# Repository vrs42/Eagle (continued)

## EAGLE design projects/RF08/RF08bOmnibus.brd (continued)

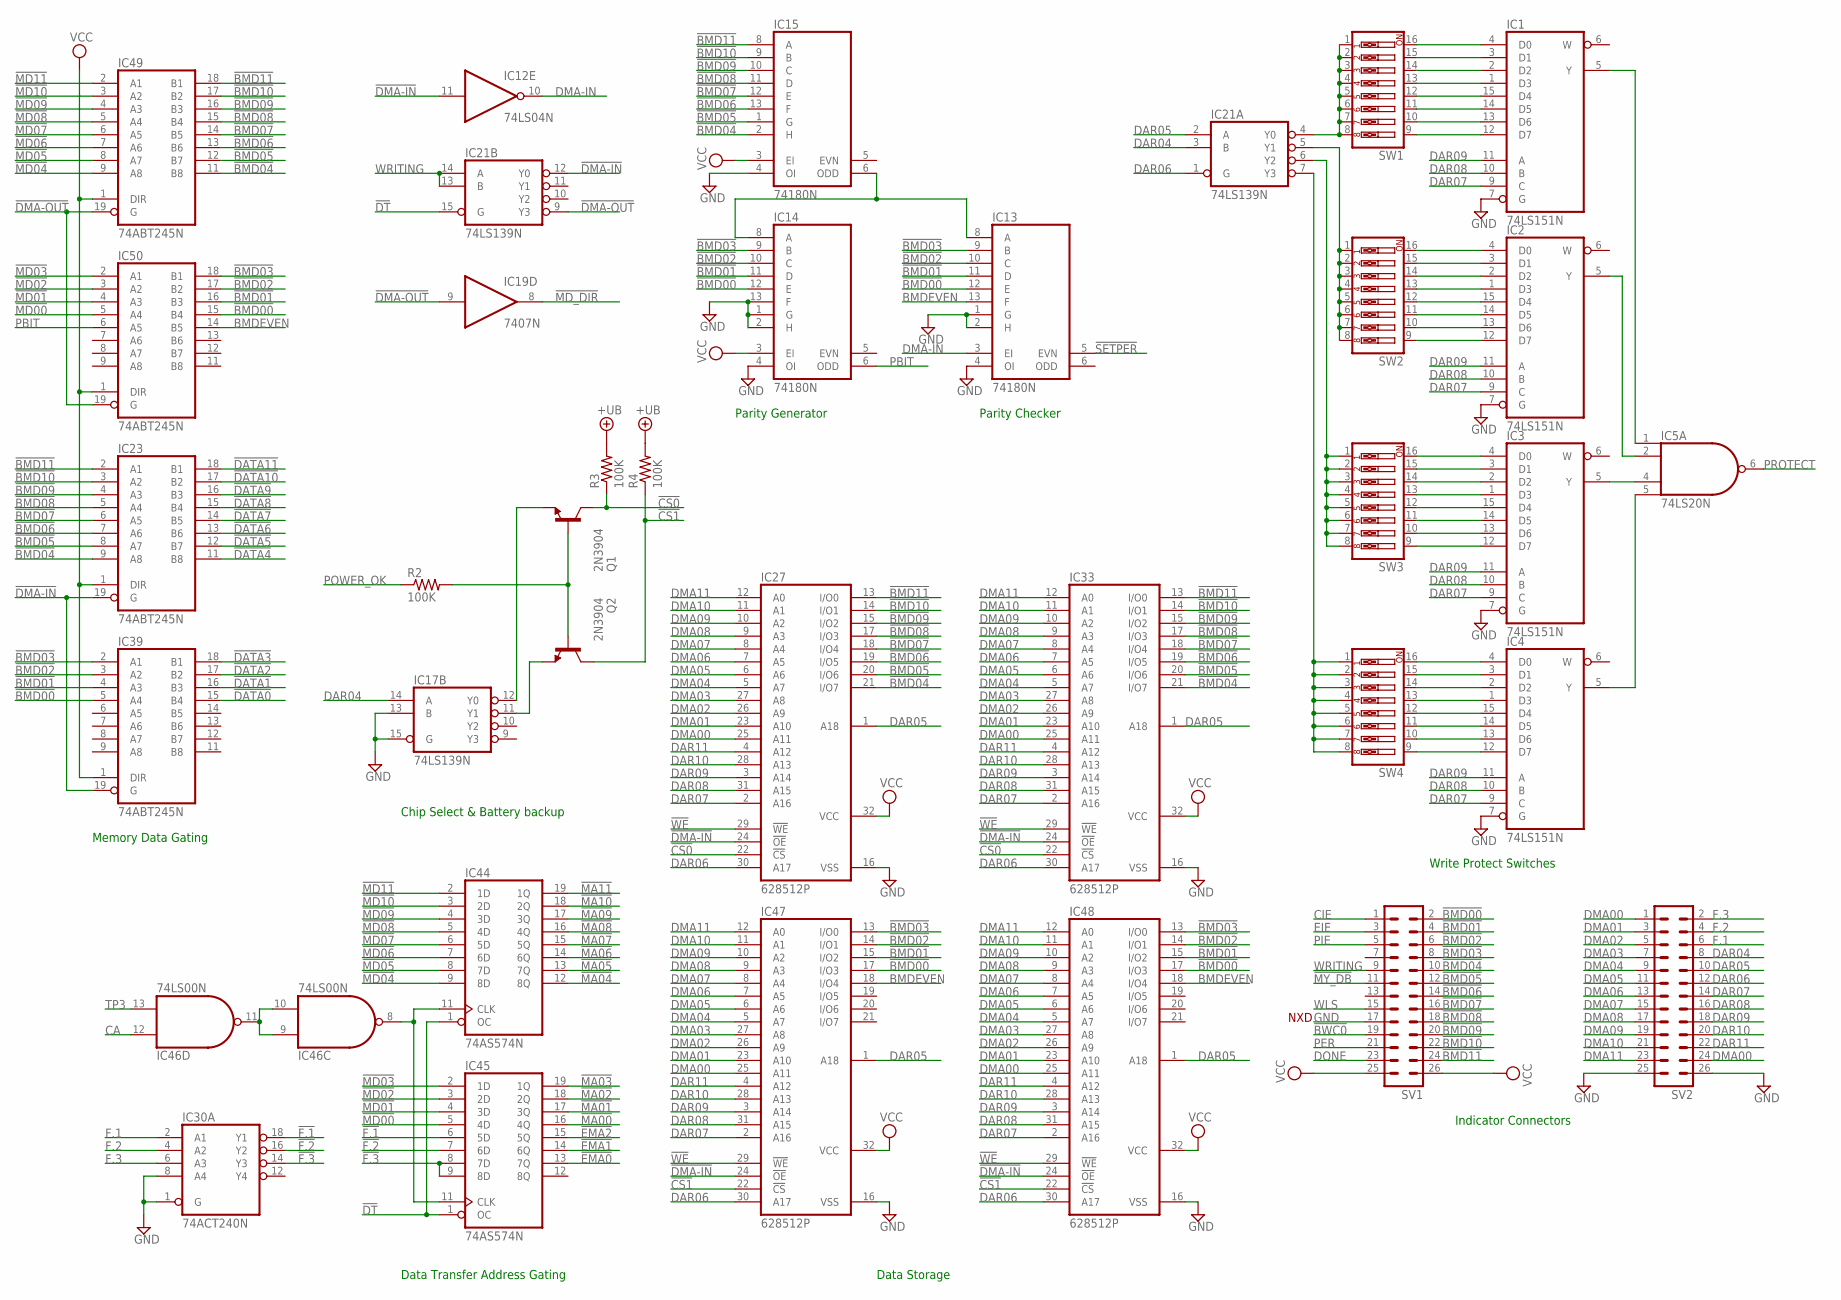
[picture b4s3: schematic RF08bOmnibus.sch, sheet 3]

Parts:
IC1, IC2, IC3, IC4: 74LS151N; DIL16
IC5: 74LS20N; DIL14
IC12: 74LS04N; DIL14
IC13, IC14, IC15: 74180N; DIL14
IC17, IC21: 74LS139N; DIL16
IC19: 7407N; DIL14
IC23, IC39, IC49, IC50: 74ABT245N; DIL20
IC27, IC33, IC47, IC48: 628512P; DIL32
IC30: 74ACT240N; DIL20
IC44, IC45: 74AS574N; DIL20
IC46: 74LS00N; DIL14
Q1, Q2: 2N3904; TO92
R2, R3, R4: 100K; 0207/10
SV1, SV2: MA13-2
SW1, SW2, SW3, SW4: SW_DIP-8; EDG-08

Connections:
!BMD00: IC13.12 (E), IC14.12 (E), IC39.5 (A4), IC47.17 (I/O3), IC48.17 (I/O3), IC50.15 (B4), SV1.2
!BMD01: IC13.11 (D), IC14.11 (D), IC39.4 (A3), IC47.15 (I/O2), IC48.15 (I/O2), IC50.16 (B3), SV1.4
!BMD02: IC13.10 (C), IC14.10 (C), IC39.3 (A2), IC47.14 (I/O1), IC48.14 (I/O1), IC50.17 (B2), SV1.6
!BMD03: IC13.9 (B), IC14.9 (B), IC39.2 (A1), IC47.13 (I/O0), IC48.13 (I/O0), IC50.18 (B1), SV1.8; also elsewhere on the board
!BMD04: IC15.2 (H), IC23.9 (A8), IC27.21 (I/O7), IC33.21 (I/O7), IC49.11 (B8), SV1.10; also elsewhere on the board
!BMD05: IC15.1 (G), IC23.8 (A7), IC27.20 (I/O6), IC33.20 (I/O6), IC49.12 (B7), SV1.12; also elsewhere on the board
!BMD06: IC15.13 (F), IC23.7 (A6), IC27.19 (I/O5), IC33.19 (I/O5), IC49.13 (B6), SV1.14; also elsewhere on the board
!BMD07: IC15.12 (E), IC23.6 (A5), IC27.18 (I/O4), IC33.18 (I/O4), IC49.14 (B5), SV1.16; also elsewhere on the board
!BMD08: IC15.11 (D), IC23.5 (A4), IC27.17 (I/O3), IC33.17 (I/O3), IC49.15 (B4), SV1.18; also elsewhere on the board
!BMD09: IC15.10 (C), IC23.4 (A3), IC27.15 (I/O2), IC33.15 (I/O2), IC49.16 (B3), SV1.20; also elsewhere on the board
!BMD10: IC15.9 (B), IC23.3 (A2), IC27.14 (I/O1), IC33.14 (I/O1), IC49.17 (B2), SV1.22; also elsewhere on the board
!BMD11: IC15.8 (A), IC23.2 (A1), IC27.13 (I/O0), IC33.13 (I/O0), IC49.18 (B1), SV1.24; also elsewhere on the board
!BWC0: SV1.19; also elsewhere on the board
!CS0: IC27.22 (!CS), IC33.22 (!CS), Q1.1 (C), R3.1
!CS1: IC47.22 (!CS), IC48.22 (!CS), Q2.1 (C), R4.1
!DATA0: IC39.15 (B4); also elsewhere on the board
!DATA1: IC39.16 (B3); also elsewhere on the board
!DATA2: IC39.17 (B2); also elsewhere on the board
!DATA3: IC39.18 (B1); also elsewhere on the board
!DATA4: IC23.11 (B8); also elsewhere on the board
!DATA5: IC23.12 (B7); also elsewhere on the board
!DATA6: IC23.13 (B6); also elsewhere on the board
!DATA7: IC23.14 (B5); also elsewhere on the board
!DATA8: IC23.15 (B4); also elsewhere on the board
!DATA9: IC23.16 (B3); also elsewhere on the board
!DATA10: IC23.17 (B2); also elsewhere on the board
!DATA11: IC23.18 (B1); also elsewhere on the board
!DMA-IN: IC12.11 (I), IC21.12 (Y0), IC23.19 (G), IC27.24 (!OE), IC33.24 (!OE), IC39.19 (G), IC47.24 (!OE), IC48.24 (!OE)
!DMA-OUT: IC19.9 (I), IC21.9 (Y3), IC49.19 (G), IC50.19 (G)
!DT: IC21.15 (G), IC44.1 (OC), IC45.1 (OC); also elsewhere on the board
!EMA0: IC45.13 (7Q); also elsewhere on the board
!EMA1: IC45.14 (6Q); also elsewhere on the board
!EMA2: IC45.15 (5Q); also elsewhere on the board
!F.1: IC30.18 (Y1), IC45.6 (5D)
!F.2: IC30.16 (Y2), IC45.7 (6D)
!F.3: IC30.14 (Y3), IC45.8 (7D), IC45.9 (8D)
!MA00: IC45.16 (4Q); also elsewhere on the board
!MA01: IC45.17 (3Q); also elsewhere on the board
!MA02: IC45.18 (2Q); also elsewhere on the board
!MA03: IC45.19 (1Q); also elsewhere on the board
!MA04: IC44.12 (8Q); also elsewhere on the board
!MA05: IC44.13 (7Q); also elsewhere on the board
!MA06: IC44.14 (6Q); also elsewhere on the board
!MA07: IC44.15 (5Q); also elsewhere on the board
!MA08: IC44.16 (4Q); also elsewhere on the board
!MA09: IC44.17 (3Q); also elsewhere on the board
!MA10: IC44.18 (2Q); also elsewhere on the board
!MA11: IC44.19 (1Q); also elsewhere on the board
!MD00: IC45.5 (4D), IC50.5 (A4); also elsewhere on the board
!MD01: IC45.4 (3D), IC50.4 (A3); also elsewhere on the board
!MD02: IC45.3 (2D), IC50.3 (A2); also elsewhere on the board
!MD03: IC45.2 (1D), IC50.2 (A1); also elsewhere on the board
!MD04: IC44.9 (8D), IC49.9 (A8); also elsewhere on the board
!MD05: IC44.8 (7D), IC49.8 (A7); also elsewhere on the board
!MD06: IC44.7 (6D), IC49.7 (A6); also elsewhere on the board
!MD07: IC44.6 (5D), IC49.6 (A5); also elsewhere on the board
!MD08: IC44.5 (4D), IC49.5 (A4); also elsewhere on the board
!MD09: IC44.4 (3D), IC49.4 (A3); also elsewhere on the board
!MD10: IC44.3 (2D), IC49.3 (A2); also elsewhere on the board
!MD11: IC44.2 (1D), IC49.2 (A1); also elsewhere on the board
!MD_DIR: IC19.8 (O); also elsewhere on the board
!MY_DB: SV1.11; also elsewhere on the board
!SETPER: IC13.5 (EVN); also elsewhere on the board
!WE: IC27.29 (!WE), IC33.29 (!WE), IC47.29 (!WE), IC48.29 (!WE); also elsewhere on the board
+UB: R3.2, R4.2
BMDEVEN: IC13.13 (F), IC47.18 (I/O4), IC48.18 (I/O4), IC50.14 (B5)
CA: IC46.12 (I0); also elsewhere on the board
CIE: SV1.1; also elsewhere on the board
DAR04: IC17.14 (A), IC21.3 (B), SV2.8; also elsewhere on the board
DAR05: IC21.2 (A), IC27.1 (A18), IC33.1 (A18), IC47.1 (A18), IC48.1 (A18), SV2.10; also elsewhere on the board
DAR06: IC21.1 (G), IC27.30 (A17), IC33.30 (A17), IC47.30 (A17), IC48.30 (A17), SV2.12; also elsewhere on the board
DAR07: IC1.9 (C), IC2.9 (C), IC3.9 (C), IC4.9 (C), IC27.2 (A16), IC33.2 (A16), IC47.2 (A16), IC48.2 (A16), SV2.14; also elsewhere on the board
DAR08: IC1.10 (B), IC2.10 (B), IC3.10 (B), IC4.10 (B), IC27.31 (A15), IC33.31 (A15), IC47.31 (A15), IC48.31 (A15), SV2.16; also elsewhere on the board
DAR09: IC1.11 (A), IC2.11 (A), IC3.11 (A), IC4.11 (A), IC27.3 (A14), IC33.3 (A14), IC47.3 (A14), IC48.3 (A14), SV2.18; also elsewhere on the board
DAR10: IC27.28 (A13), IC33.28 (A13), IC47.28 (A13), IC48.28 (A13), SV2.20; also elsewhere on the board
DAR11: IC27.4 (A12), IC33.4 (A12), IC47.4 (A12), IC48.4 (A12), SV2.22; also elsewhere on the board
DMA00: IC27.25 (A11), IC33.25 (A11), IC47.25 (A11), IC48.25 (A11), SV2.1, SV2.24; also elsewhere on the board
DMA01: IC27.23 (A10), IC33.23 (A10), IC47.23 (A10), IC48.23 (A10), SV2.3; also elsewhere on the board
DMA02: IC27.26 (A9), IC33.26 (A9), IC47.26 (A9), IC48.26 (A9), SV2.5; also elsewhere on the board
DMA03: IC27.27 (A8), IC33.27 (A8), IC47.27 (A8), IC48.27 (A8), SV2.7; also elsewhere on the board
DMA04: IC27.5 (A7), IC33.5 (A7), IC47.5 (A7), IC48.5 (A7), SV2.9; also elsewhere on the board
DMA05: IC27.6 (A6), IC33.6 (A6), IC47.6 (A6), IC48.6 (A6), SV2.11; also elsewhere on the board
DMA06: IC27.7 (A5), IC33.7 (A5), IC47.7 (A5), IC48.7 (A5), SV2.13; also elsewhere on the board
DMA07: IC27.8 (A4), IC33.8 (A4), IC47.8 (A4), IC48.8 (A4), SV2.15; also elsewhere on the board
DMA08: IC27.9 (A3), IC33.9 (A3), IC47.9 (A3), IC48.9 (A3), SV2.17; also elsewhere on the board
DMA09: IC27.10 (A2), IC33.10 (A2), IC47.10 (A2), IC48.10 (A2), SV2.19; also elsewhere on the board
DMA10: IC27.11 (A1), IC33.11 (A1), IC47.11 (A1), IC48.11 (A1), SV2.21; also elsewhere on the board
DMA11: IC27.12 (A0), IC33.12 (A0), IC47.12 (A0), IC48.12 (A0), SV2.23; also elsewhere on the board
DMA-IN: IC12.10 (O), IC13.3 (EI)
DONE: SV1.23; also elsewhere on the board
EIE: SV1.3; also elsewhere on the board
F.1: IC30.2 (A1), SV2.6; also elsewhere on the board
F.2: IC30.4 (A2), SV2.4; also elsewhere on the board
F.3: IC30.6 (A3), SV2.2; also elsewhere on the board
GND: IC1.7 (G), IC1.8 (GND), IC2.7 (G), IC2.8 (GND), IC3.7 (G), IC3.8 (GND), IC4.7 (G), IC4.8 (GND), IC5.7 (GND), IC12.7 (GND), IC13.1 (G), IC13.2 (H), IC13.4 (OI), IC13.7 (GND), IC14.1 (G), IC14.2 (H), IC14.4 (OI), IC14.7 (GND), IC14.13 (F), IC15.4 (OI), IC15.7 (GND), IC17.8 (GND), IC17.13 (B), IC17.15 (G), IC19.7 (GND), IC21.8 (GND), IC23.10 (GND), IC27.16 (VSS), IC30.1 (G), IC30.8 (A4), IC30.10 (GND), IC33.16 (VSS), IC39.10 (GND), IC44.10 (GND), IC45.10 (GND), IC46.7 (GND), IC47.16 (VSS), IC48.16 (VSS), IC49.10 (GND), IC50.10 (GND), SV1.17, SV2.25, SV2.26; also elsewhere on the board
unnamed: IC21.4 (Y0), SW1.1, SW1.2, SW1.3, SW1.4, SW1.5, SW1.6, SW1.7, SW1.8
unnamed: IC13.8 (A), IC14.8 (A), IC15.6 (ODD)
unnamed: IC2.5 (Y), IC5.2 (I1)
unnamed: IC21.5 (Y1), SW2.1, SW2.2, SW2.3, SW2.4, SW2.5, SW2.6, SW2.7, SW2.8
unnamed: IC21.6 (Y2), SW3.1, SW3.2, SW3.3, SW3.4, SW3.5, SW3.6, SW3.7, SW3.8
unnamed: IC21.7 (Y3), SW4.1, SW4.2, SW4.3, SW4.4, SW4.5, SW4.6, SW4.7, SW4.8
unnamed: IC3.5 (Y), IC5.4 (I2)
unnamed: IC1.5 (Y), IC5.1 (I0)
unnamed: IC4.5 (Y), IC5.5 (I3)
unnamed: IC44.11 (CLK), IC45.11 (CLK), IC46.8 (O)
unnamed: IC46.9 (I0), IC46.10 (I1), IC46.11 (O)
unnamed: IC1.4 (D0), SW1.16
unnamed: IC1.3 (D1), SW1.15
unnamed: IC1.2 (D2), SW1.14
unnamed: IC1.1 (D3), SW1.13
unnamed: IC1.14 (D5), SW1.11
unnamed: IC1.13 (D6), SW1.10
unnamed: IC1.12 (D7), SW1.9
unnamed: IC1.15 (D4), SW1.12
unnamed: IC2.4 (D0), SW2.16
unnamed: IC2.3 (D1), SW2.15
unnamed: IC2.2 (D2), SW2.14
unnamed: IC2.1 (D3), SW2.13
unnamed: IC2.14 (D5), SW2.11
unnamed: IC2.13 (D6), SW2.10
unnamed: IC2.12 (D7), SW2.9
unnamed: IC3.4 (D0), SW3.16
unnamed: IC3.3 (D1), SW3.15
unnamed: IC3.2 (D2), SW3.14
unnamed: IC3.1 (D3), SW3.13
unnamed: IC3.14 (D5), SW3.11
unnamed: IC3.13 (D6), SW3.10
unnamed: IC3.12 (D7), SW3.9
unnamed: IC4.4 (D0), SW4.16
unnamed: IC4.3 (D1), SW4.15
unnamed: IC4.2 (D2), SW4.14
unnamed: IC4.1 (D3), SW4.13
unnamed: IC4.14 (D5), SW4.11
unnamed: IC4.13 (D6), SW4.10
unnamed: IC4.12 (D7), SW4.9
unnamed: IC4.15 (D4), SW4.12
unnamed: IC3.15 (D4), SW3.12
unnamed: IC2.15 (D4), SW2.12
unnamed: IC17.12 (Y0), Q1.3 (E)
unnamed: Q1.2 (B), Q2.2 (B), R2.2
unnamed: IC17.11 (Y1), Q2.3 (E)
PBIT: IC14.6 (ODD), IC50.6 (A5)
PER: SV1.21; also elsewhere on the board
PIE: SV1.5; also elsewhere on the board
POWER_OK: R2.1; also elsewhere on the board
PROTECT: IC5.6 (O); also elsewhere on the board
TP3: IC46.13 (I1); also elsewhere on the board
VCC: IC1.16 (VCC), IC2.16 (VCC), IC3.16 (VCC), IC4.16 (VCC), IC5.14 (VCC), IC12.14 (VCC), IC13.14 (VCC), IC14.3 (EI), IC14.14 (VCC), IC15.3 (EI), IC15.14 (VCC), IC17.16 (VCC), IC19.14 (VCC), IC21.16 (VCC), IC23.1 (DIR), IC23.20 (VCC), IC27.32 (VCC), IC30.20 (VCC), IC33.32 (VCC), IC39.1 (DIR), IC39.20 (VCC), IC44.20 (VCC), IC45.20 (VCC), IC46.14 (VCC), IC47.32 (VCC), IC48.32 (VCC), IC49.1 (DIR), IC49.20 (VCC), IC50.1 (DIR), IC50.20 (VCC), SV1.25, SV1.26; also elsewhere on the board
WLS: SV1.15; also elsewhere on the board
WRITING: IC21.13 (B), IC21.14 (A), SV1.9; also elsewhere on the board

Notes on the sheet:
Parity Generator
Parity Checker
Memory Data Gating
Write Protect Switches
Data Storage
Indicator Connectors
NXD
Data Transfer Address Gating
Chip Select & Battery backup

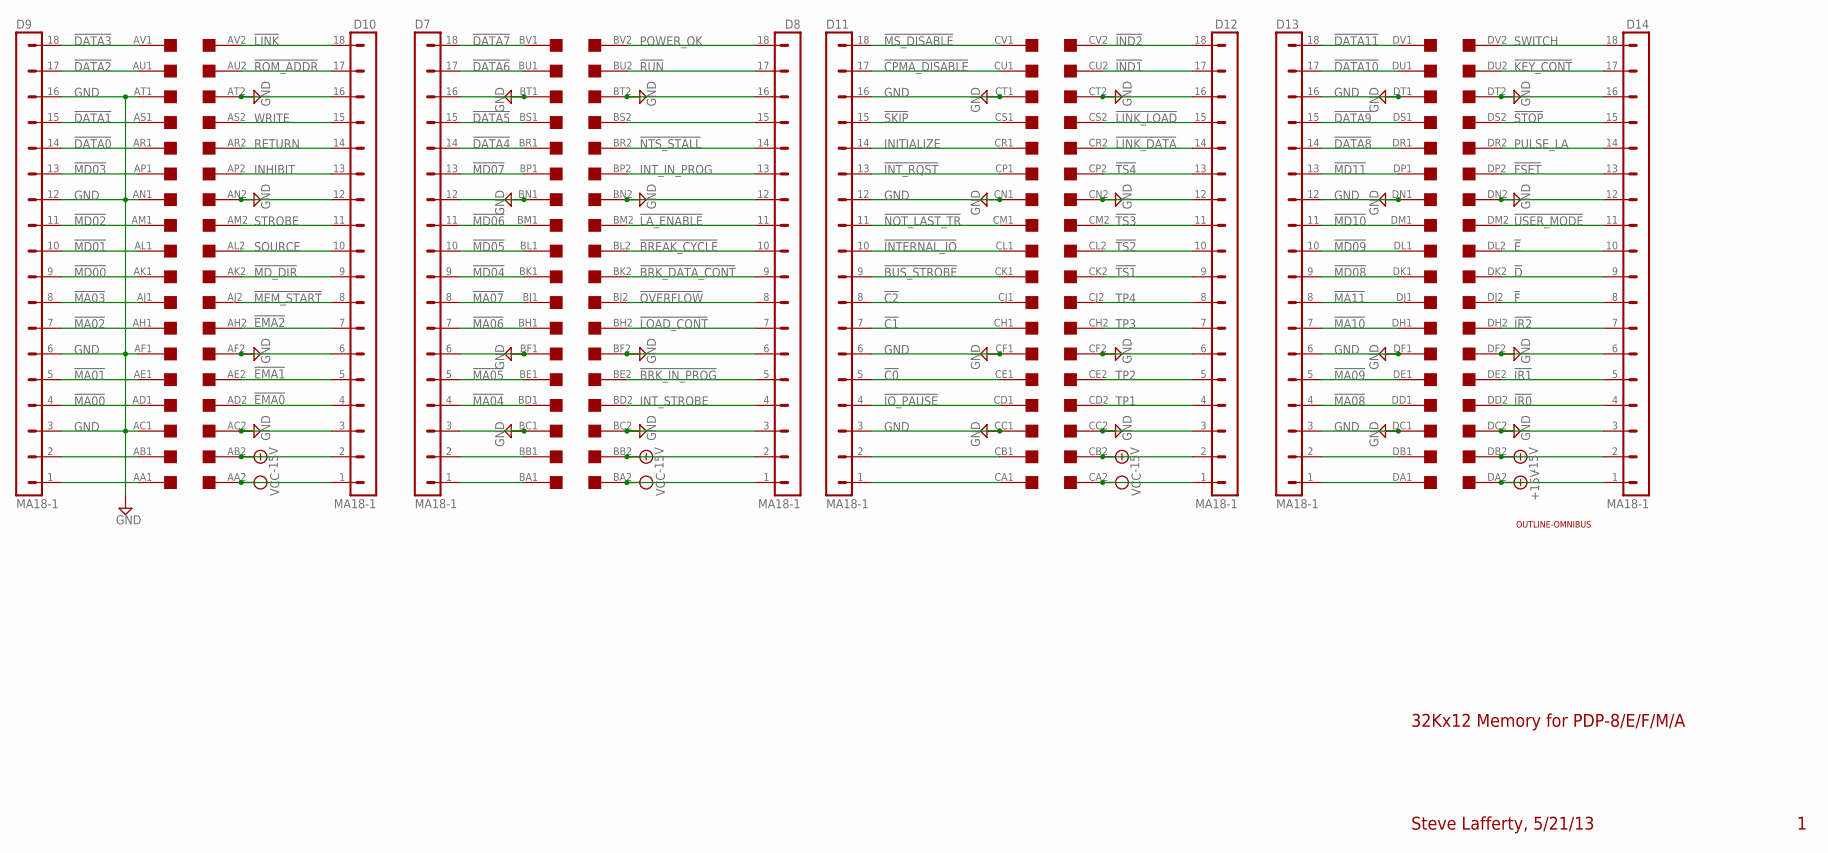
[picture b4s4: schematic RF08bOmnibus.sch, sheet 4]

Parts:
D7, D8, D9, D10, D11, D12, D13, D14: MA18-1
U$15: OUTLINE-OMNIBUS; OMNIBUS
U$19: QUAD; EDGE-CON8

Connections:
!BREAK_CYCLE: D8.10, U$19.BL2; also elsewhere on the board
!BRK_DATA_CONT: D8.9, U$19.BK2; also elsewhere on the board
!BRK_IN_PROG: D8.5, U$19.BE2; also elsewhere on the board
!BUS_STROBE: D11.9, U$19.CK1
!C0: D11.5, U$19.CE1; also elsewhere on the board
!C1: D11.7, U$19.CH1; also elsewhere on the board
!C2: D11.8, U$19.CJ1
!CPMA_DISABLE: D11.17, U$19.CU1; also elsewhere on the board
!D: D14.9, U$19.DK2
!DATA0: D9.14, U$19.AR1; also elsewhere on the board
!DATA1: D9.15, U$19.AS1; also elsewhere on the board
!DATA2: D9.17, U$19.AU1; also elsewhere on the board
!DATA3: D9.18, U$19.AV1; also elsewhere on the board
!DATA4: D7.14, U$19.BR1; also elsewhere on the board
!DATA5: D7.15, U$19.BS1; also elsewhere on the board
!DATA6: D7.17, U$19.BU1; also elsewhere on the board
!DATA7: D7.18, U$19.BV1; also elsewhere on the board
!DATA8: D13.14, U$19.DR1; also elsewhere on the board
!DATA9: D13.15, U$19.DS1; also elsewhere on the board
!DATA10: D13.17, U$19.DU1; also elsewhere on the board
!DATA11: D13.18, U$19.DV1; also elsewhere on the board
!E: D14.10, U$19.DL2
!EMA0: D10.4, U$19.AD2; also elsewhere on the board
!EMA1: D10.5, U$19.AE2; also elsewhere on the board
!EMA2: D10.7, U$19.AH2; also elsewhere on the board
!F: D14.8, U$19.DJ2
!FSET: D14.13, U$19.DP2
!IND1: D12.17, U$19.CU2
!IND2: D12.18, U$19.CV2
!INTERNAL_IO: D11.10, U$19.CL1; also elsewhere on the board
!INT_RQST: D11.13, U$19.CP1
!IO_PAUSE: D11.4, U$19.CD1; also elsewhere on the board
!IR0: D14.4, U$19.DD2
!IR1: D14.5, U$19.DE2
!IR2: D14.7, U$19.DH2
!KEY_CONT: D14.17, U$19.DU2
!LA_ENABLE: D8.11, U$19.BM2
!LINK: D10.18, U$19.AV2
!LINK_DATA: D12.14, U$19.CR2
!LINK_LOAD: D12.15, U$19.CS2
!LOAD_CONT: D8.7, U$19.BH2; also elsewhere on the board
!MA00: D9.4, U$19.AD1; also elsewhere on the board
!MA01: D9.5, U$19.AE1; also elsewhere on the board
!MA02: D9.7, U$19.AH1; also elsewhere on the board
!MA03: D9.8, U$19.AJ1; also elsewhere on the board
!MA04: D7.4, U$19.BD1; also elsewhere on the board
!MA05: D7.5, U$19.BE1; also elsewhere on the board
!MA06: D7.7, U$19.BH1; also elsewhere on the board
!MA07: D7.8, U$19.BJ1; also elsewhere on the board
!MA08: D13.4, U$19.DD1; also elsewhere on the board
!MA09: D13.5, U$19.DE1; also elsewhere on the board
!MA10: D13.7, U$19.DH1; also elsewhere on the board
!MA11: D13.8, U$19.DJ1; also elsewhere on the board
!MD00: D9.9, U$19.AK1; also elsewhere on the board
!MD01: D9.10, U$19.AL1; also elsewhere on the board
!MD02: D9.11, U$19.AM1; also elsewhere on the board
!MD03: D9.13, U$19.AP1; also elsewhere on the board
!MD04: D7.9, U$19.BK1; also elsewhere on the board
!MD05: D7.10, U$19.BL1; also elsewhere on the board
!MD06: D7.11, U$19.BM1; also elsewhere on the board
!MD07: D7.13, U$19.BP1; also elsewhere on the board
!MD08: D13.9, U$19.DK1; also elsewhere on the board
!MD09: D13.10, U$19.DL1; also elsewhere on the board
!MD10: D13.11, U$19.DM1; also elsewhere on the board
!MD11: D13.13, U$19.DP1; also elsewhere on the board
!MD_DIR: D10.9, U$19.AK2; also elsewhere on the board
!MEM_START: D10.8, U$19.AJ2
!MS_DISABLE: D11.18, U$19.CV1; also elsewhere on the board
!NOT_LAST_TR: D11.11, U$19.CM1
!NTS_STALL: D8.14, U$19.BR2
!OVERFLOW: D8.8, U$19.BJ2; also elsewhere on the board
!ROM_ADDR: D10.17, U$19.AU2
!RUN: D8.17, U$19.BU2
!SKIP: D11.15, U$19.CS1; also elsewhere on the board
!STOP: D14.15, U$19.DS2
!TS1: D12.9, U$19.CK2
!TS2: D12.10, U$19.CL2
!TS3: D12.11, U$19.CM2
!TS4: D12.13, U$19.CP2; also elsewhere on the board
!USER_MODE: D14.11, U$19.DM2
+15V: D14.1, U$19.DA2
-15V: D8.2, D10.2, D12.2, D14.2, U$19.AB2, U$19.BB2, U$19.CB2, U$19.DB2
GND: D7.3, D7.6, D7.12, D7.16, D8.3, D8.6, D8.12, D8.16, D9.3, D9.6, D9.12, D9.16, D10.3, D10.6, D10.12, D10.16, D11.3, D11.6, D11.12, D11.16, D12.3, D12.6, D12.12, D12.16, D13.3, D13.6, D13.12, D13.16, D14.3, D14.6, D14.12, D14.16, U$19.AC1, U$19.AC2, U$19.AF1, U$19.AF2, U$19.AN1, U$19.AN2, U$19.AT1, U$19.AT2, U$19.BC1, U$19.BC2, U$19.BF1, U$19.BF2, U$19.BN1, U$19.BN2, U$19.BT1, U$19.BT2, U$19.CC1, U$19.CC2, U$19.CF1, U$19.CF2, U$19.CN1, U$19.CN2, U$19.CT1, U$19.CT2, U$19.DC1, U$19.DC2, U$19.DF1, U$19.DF2, U$19.DN1, U$19.DN2, U$19.DT1, U$19.DT2; also elsewhere on the board
INHIBIT: D10.13, U$19.AP2
INITIALIZE: D11.14, U$19.CR1; also elsewhere on the board
INT_IN_PROG: D8.13, U$19.BP2
INT_STROBE: D8.4, U$19.BD2; also elsewhere on the board
unnamed: D13.1, U$19.DA1
unnamed: D13.2, U$19.DB1
unnamed: D9.2, U$19.AB1
unnamed: D9.1, U$19.AA1
unnamed: D7.2, U$19.BB1
unnamed: D7.1, U$19.BA1
unnamed: D11.1, U$19.CA1
unnamed: D8.15, U$19.BS2
unnamed: D11.2, U$19.CB1
POWER_OK: D8.18, U$19.BV2; also elsewhere on the board
PULSE_LA: D14.14, U$19.DR2
RETURN: D10.14, U$19.AR2
SOURCE: D10.10, U$19.AL2
STROBE: D10.11, U$19.AM2
SWITCH: D14.18, U$19.DV2
TP1: D12.4, U$19.CD2; also elsewhere on the board
TP2: D12.5, U$19.CE2
TP3: D12.7, U$19.CH2; also elsewhere on the board
TP4: D12.8, U$19.CJ2; also elsewhere on the board
VCC: D8.1, D10.1, D12.1, U$19.AA2, U$19.BA2, U$19.CA2; also elsewhere on the board
WRITE: D10.15, U$19.AS2

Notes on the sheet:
32Kx12 Memory for PDP-8/E/F/M/A
Steve Lafferty, 5/21/13

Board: 2 copper layers, 148 parts (0 on the bottom side), 306 nets, no tracks yet.

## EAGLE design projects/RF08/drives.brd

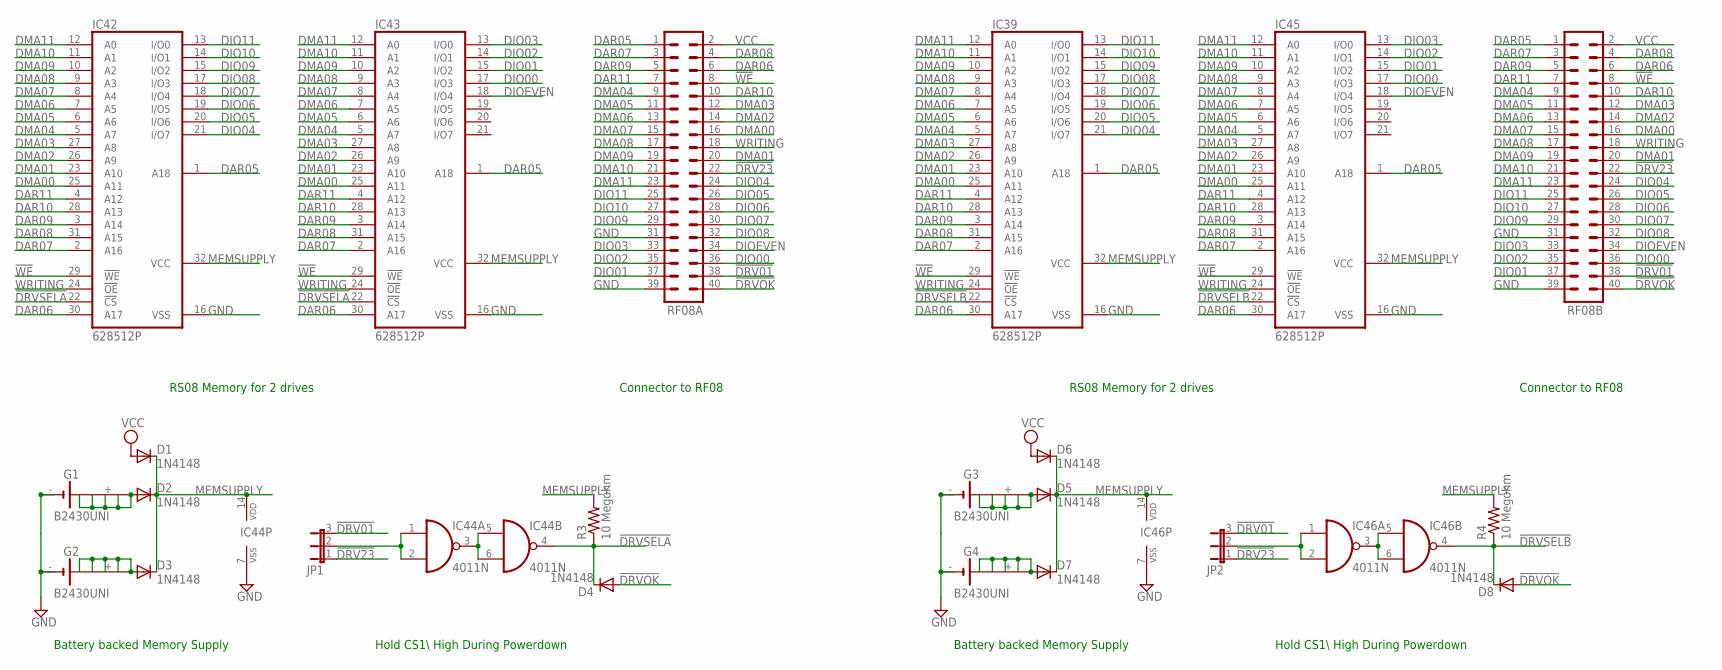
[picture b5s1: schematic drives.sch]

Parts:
D1, D2, D3, D4, D5, D6, D7, D8: 1N4148; DO35-10
G1, G2, G3, G4: B2430UNI
IC39, IC42, IC43, IC45: 628512P; DIL32
IC44, IC46: 4011N; DIL14
JP1, JP2: JP2E; JP2
R3, R4: 10 Megohm; 0207/10
RF08A, RF08B: MA20-2

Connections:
!DRV01: JP1.3, JP2.3, RF08A.38, RF08B.38
!DRV23: JP1.1, JP2.1, RF08A.22, RF08B.22
!DRVOK: D4.A, D8.A, RF08A.40, RF08B.40
!DRVSELA: D4.C, IC42.22 (!CS), IC43.22 (!CS), IC44.4 (O), R3.1
!DRVSELB: D8.C, IC39.22 (!CS), IC45.22 (!CS), IC46.4 (O), R4.1
!WE: IC39.29 (!WE), IC42.29 (!WE), IC43.29 (!WE), IC45.29 (!WE), RF08A.8, RF08B.8
DAR05: IC39.1 (A18), IC42.1 (A18), IC43.1 (A18), IC45.1 (A18), RF08A.1, RF08B.1
DAR06: IC39.30 (A17), IC42.30 (A17), IC43.30 (A17), IC45.30 (A17), RF08A.6, RF08B.6
DAR07: IC39.2 (A16), IC42.2 (A16), IC43.2 (A16), IC45.2 (A16), RF08A.3, RF08B.3
DAR08: IC39.31 (A15), IC42.31 (A15), IC43.31 (A15), IC45.31 (A15), RF08A.4, RF08B.4
DAR09: IC39.3 (A14), IC42.3 (A14), IC43.3 (A14), IC45.3 (A14), RF08A.5, RF08B.5
DAR10: IC39.28 (A13), IC42.28 (A13), IC43.28 (A13), IC45.28 (A13), RF08A.10, RF08B.10
DAR11: IC39.4 (A12), IC42.4 (A12), IC43.4 (A12), IC45.4 (A12), RF08A.7, RF08B.7
DIO00: IC43.17 (I/O3), IC45.17 (I/O3), RF08A.36, RF08B.36
DIO01: IC43.15 (I/O2), IC45.15 (I/O2), RF08A.37, RF08B.37
DIO02: IC43.14 (I/O1), IC45.14 (I/O1), RF08A.35, RF08B.35
DIO03: IC43.13 (I/O0), IC45.13 (I/O0), RF08A.33, RF08B.33
DIO04: IC39.21 (I/O7), IC42.21 (I/O7), RF08A.24, RF08B.24
DIO05: IC39.20 (I/O6), IC42.20 (I/O6), RF08A.26, RF08B.26
DIO06: IC39.19 (I/O5), IC42.19 (I/O5), RF08A.28, RF08B.28
DIO07: IC39.18 (I/O4), IC42.18 (I/O4), RF08A.30, RF08B.30
DIO08: IC39.17 (I/O3), IC42.17 (I/O3), RF08A.32, RF08B.32
DIO09: IC39.15 (I/O2), IC42.15 (I/O2), RF08A.29, RF08B.29
DIO10: IC39.14 (I/O1), IC42.14 (I/O1), RF08A.27, RF08B.27
DIO11: IC39.13 (I/O0), IC42.13 (I/O0), RF08A.25, RF08B.25
DIOEVEN: IC43.18 (I/O4), IC45.18 (I/O4), RF08A.34, RF08B.34
DMA00: IC39.25 (A11), IC42.25 (A11), IC43.25 (A11), IC45.25 (A11), RF08A.16, RF08B.16
DMA01: IC39.23 (A10), IC42.23 (A10), IC43.23 (A10), IC45.23 (A10), RF08A.20, RF08B.20
DMA02: IC39.26 (A9), IC42.26 (A9), IC43.26 (A9), IC45.26 (A9), RF08A.14, RF08B.14
DMA03: IC39.27 (A8), IC42.27 (A8), IC43.27 (A8), IC45.27 (A8), RF08A.12, RF08B.12
DMA04: IC39.5 (A7), IC42.5 (A7), IC43.5 (A7), IC45.5 (A7), RF08A.9, RF08B.9
DMA05: IC39.6 (A6), IC42.6 (A6), IC43.6 (A6), IC45.6 (A6), RF08A.11, RF08B.11
DMA06: IC39.7 (A5), IC42.7 (A5), IC43.7 (A5), IC45.7 (A5), RF08A.13, RF08B.13
DMA07: IC39.8 (A4), IC42.8 (A4), IC43.8 (A4), IC45.8 (A4), RF08A.15, RF08B.15
DMA08: IC39.9 (A3), IC42.9 (A3), IC43.9 (A3), IC45.9 (A3), RF08A.17, RF08B.17
DMA09: IC39.10 (A2), IC42.10 (A2), IC43.10 (A2), IC45.10 (A2), RF08A.19, RF08B.19
DMA10: IC39.11 (A1), IC42.11 (A1), IC43.11 (A1), IC45.11 (A1), RF08A.21, RF08B.21
DMA11: IC39.12 (A0), IC42.12 (A0), IC43.12 (A0), IC45.12 (A0), RF08A.23, RF08B.23
GND: G1.-, G1.-@1 (-), G2.-, G2.-@1 (-), G3.-, G3.-@1 (-), G4.-, G4.-@1 (-), IC39.16 (VSS), IC42.16 (VSS), IC43.16 (VSS), IC44.7 (VSS), IC45.16 (VSS), IC46.7 (VSS), RF08A.31, RF08A.39, RF08B.31, RF08B.39
MEMSUPPLY: D1.C, D2.C, D3.C, D5.C, D6.C, D7.C, IC39.32 (VCC), IC42.32 (VCC), IC43.32 (VCC), IC44.14 (VDD), IC45.32 (VCC), IC46.14 (VDD), R3.2, R4.2
unnamed: IC44.3 (O), IC44.5 (I0), IC44.6 (I1)
unnamed: IC44.1 (I0), IC44.2 (I1), JP1.2
unnamed: D7.A, G4.+, G4.+@1 (+), G4.+@2 (+), G4.+@3 (+), G4.+@4 (+)
unnamed: IC46.3 (O), IC46.5 (I0), IC46.6 (I1)
unnamed: IC46.1 (I0), IC46.2 (I1), JP2.2
unnamed: D5.A, G3.+, G3.+@1 (+), G3.+@2 (+), G3.+@3 (+), G3.+@4 (+)
unnamed: D3.A, G2.+, G2.+@1 (+), G2.+@2 (+), G2.+@3 (+), G2.+@4 (+)
unnamed: D2.A, G1.+, G1.+@1 (+), G1.+@2 (+), G1.+@3 (+), G1.+@4 (+)
VCC: D1.A, D6.A, RF08A.2, RF08B.2
WRITING: IC39.24 (!OE), IC42.24 (!OE), IC43.24 (!OE), IC45.24 (!OE), RF08A.18, RF08B.18

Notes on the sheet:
Hold CS1\\ High During Powerdown
Battery backed Memory Supply
RS08 Memory for 2 drives
Connector to RF08

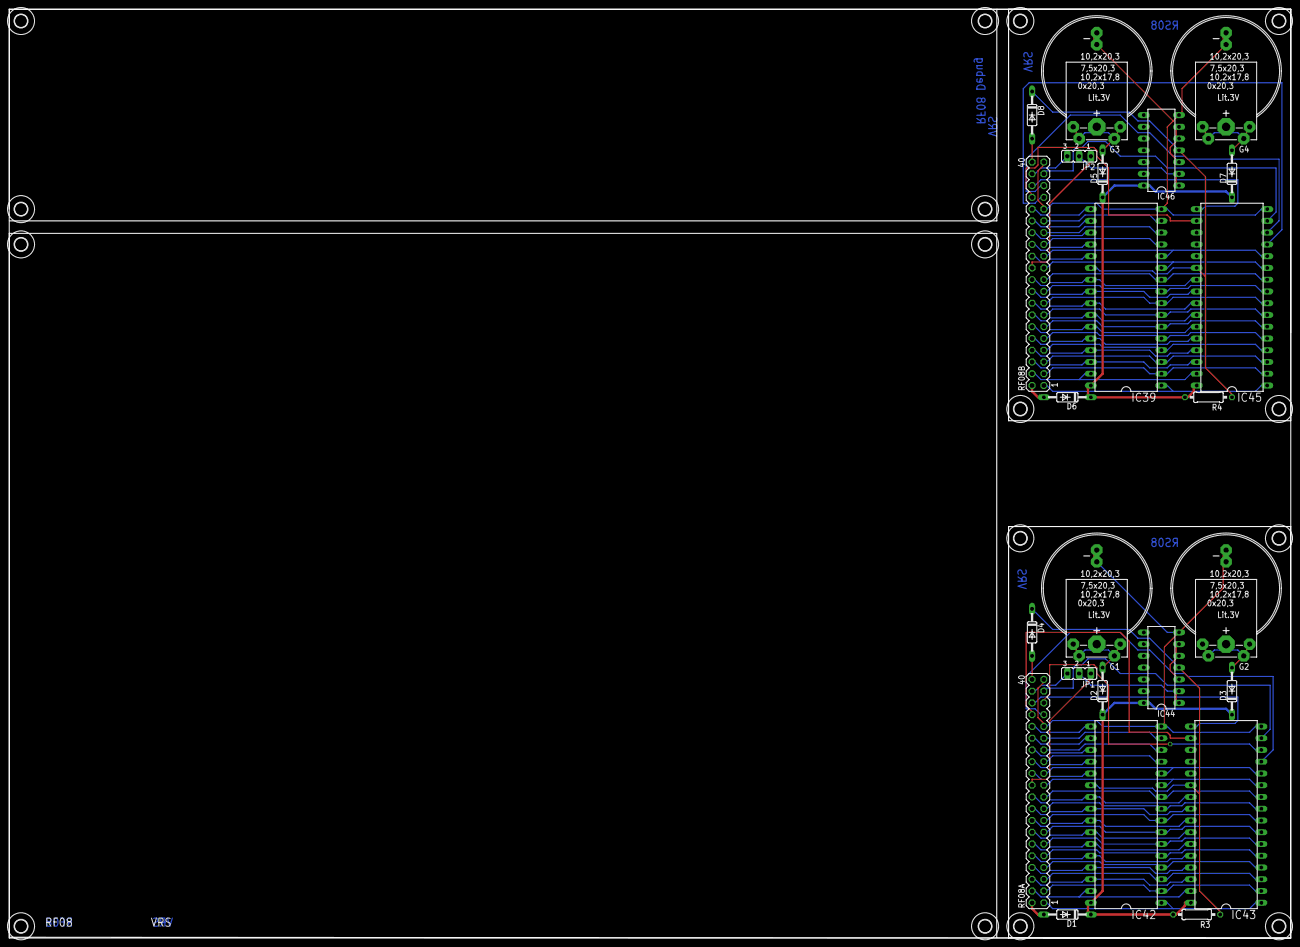
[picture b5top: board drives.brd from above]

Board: 2 copper layers, 276.9 x 200.7 mm, 41 parts (0 on the bottom side), 50 nets.

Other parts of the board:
U$1, U$2, U$3, U$4, U$5, U$6, U$7, U$8, U$9, U$10, U$11, U$12, U$13, U$14, U$16, U$17: 2,8
U$18: SIERRA-PROTO
